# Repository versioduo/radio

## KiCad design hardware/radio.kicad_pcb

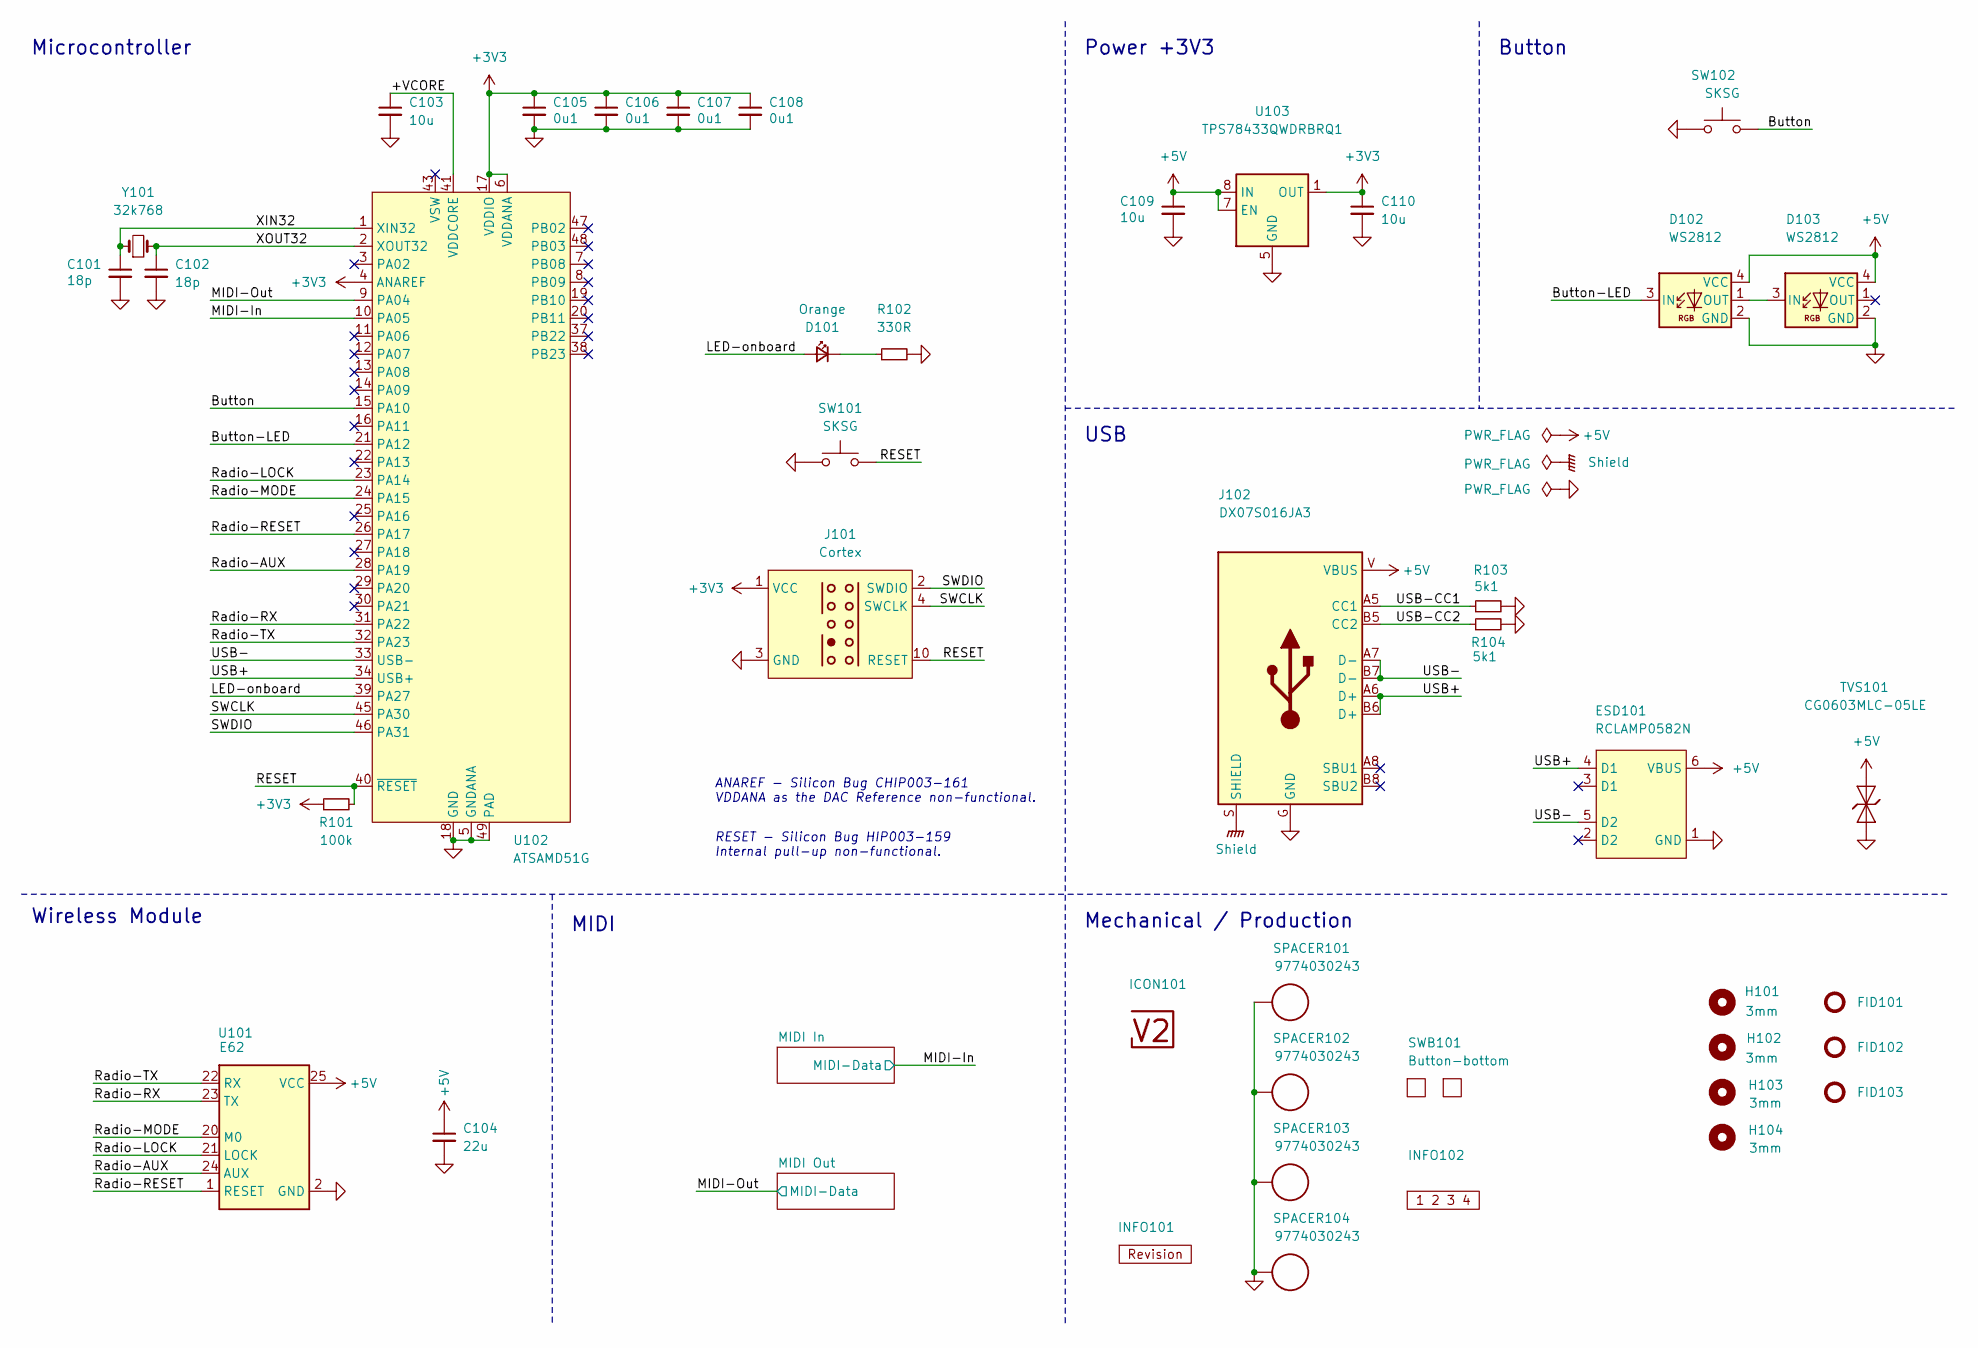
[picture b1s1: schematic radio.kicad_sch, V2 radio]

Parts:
C101, C102: 18p; C_0603; Rating 50V; Mouser 810-CGA3E2C0G1H180J
C103: 10u; C_0603; Rating 10V; Mouser 810-C1608X6S1A106M
C104: 22u; C_1210; Rating 25V; Mouser 810-CGA6P3X7R1E226M5
C105, C106, C107, C108: 0u1; C_0603; Rating 50V; Mouser 810-CGA3E2X7R1H104MA
C109, C110: 10u; C_0805; Rating 25V; Mouser 810-C2012X5R1E106K
D101: Orange; LED_0603; Rating 605nm; Mouser 755-SML-D12D1WT86
D102, D103: WS2812; WS2812-2020; Rating 15mA; LCSC C965555
ESD101: RCLAMP0582N; SLP1210N6; Rating 20kV; Mouser 947-RCLAMP0582N.TCT
FID101, FID102, FID103: Fiducial_Paste; Fiducial_0.5mm_Mask1mm_Paste
H101, H102, H103, H104: 3mm; MountingHole_3mm
ICON101: V2-logo; Logo_Small
INFO101: Revision
INFO102: Layer_Numbers
J101: Cortex
J102: DX07S016JA3; JAE_DX07S016JA3; Rating USB2.0; Mouser 656-DX07S016JA3R1500
R101: 100k; R_0603; Rating 100mW; Mouser 71-CRCW0603100KFKEAC
R102: 330R; R_0603; Rating 100mW; Mouser 71-CRCW0603330RFKEAC
R103, R104: 5k1; R_0603; Rating 100mW; Mouser 71-CRCW06035K10FKEAC
SPACER101, SPACER102, SPACER103, SPACER104: 9774030243; Rating 3mm; Mouser 710-9774030243R
SW101, SW102: SKSG; Rating 1.6N; Mouser 688-SKSGACE010
SWB101: Button-bottom; PCB_Button-bottom
TVS101: CG0603MLC-05LE; D_0603; Rating 5V; Mouser 652-CG0603MLC-05LE
U101: E62; Rating 433Mhz
U102: ATSAMD51G; QFN-48-1EP_7x7mm_P0.5mm_EP5.45x5.45mm_ThermalVias; Rating Cortex-M4F; Mouser 556-ATSAMD51G19AMU
U103: TPS78433QWDRBRQ1; VSON-8-1_3x3mm_P0.65_EP1.65x2.4mm; Rating 300mA; Mouser 595-TPS78433QWDRBRQ1
Y101: 32k768; Crystal_SMD_3215-2Pin_3.2x1.5mm; Rating 10ppm; Mouser 815-ABS0716632.768KT

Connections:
+3V3: C105.1, C106.1, C107.1, C108.1, C110.1, J101.1 (VCC), R101.1, U102.4 (ANAREF), U102.6 (VDDANA), U102.17 (VDDIO), U102.36 (VDDIO), U102.44 (VDDIO), U103.1 (OUT); also elsewhere on the board
+5V: C104.1, C109.1, D102.4 (VCC), D103.4 (VCC), ESD101.6 (VBUS), J102.V (VBUS), TVS101.2 (A), U101.25 (VCC), U103.7 (EN), U103.8 (IN); also elsewhere on the board
/+VCORE: C103.1, U102.41 (VDDCORE)
/Button: SW102.2, U102.15 (PA10)
/Button-LED: D102.3 (IN), U102.21 (PA12)
/LED-onboard: D101.2 (A), U102.39 (PA27)
/MIDI-In: U102.10 (PA05); also elsewhere on the board
/MIDI-Out: U102.9 (PA04); also elsewhere on the board
/RESET: J101.10 (RESET), R101.2, SW101.2, U102.40 (~RESET)
/Radio-AUX: U101.24 (AUX), U102.28 (PA19)
/Radio-LOCK: U101.21 (LOCK), U102.23 (PA14)
/Radio-MODE: U101.20 (M0), U102.24 (PA15)
/Radio-RESET: U101.1 (RESET), U102.26 (PA17)
/Radio-RX: U101.23 (TX), U102.31 (PA22)
/Radio-TX: U101.22 (RX), U102.32 (PA23)
/SWCLK: J101.4 (SWCLK), U102.45 (PA30)
/SWDIO: J101.2 (SWDIO), U102.46 (PA31)
/Shield: J102.S (SHIELD)
/USB+: ESD101.4 (D1), J102.A6 (D+), J102.B6 (D+), U102.34 (USB+)
/USB-: ESD101.5 (D2), J102.A7 (D-), J102.B7 (D-), U102.33 (USB-)
/USB-CC1: J102.A5 (CC1), R103.1
/USB-CC2: J102.B5 (CC2), R104.1
/XIN32: C101.1, U102.1 (XIN32), Y101.1
/XOUT32: C102.1, U102.2 (XOUT32), Y101.2
GND: C101.2, C102.2, C103.2, C104.2, C105.2, C106.2, C107.2, C108.2, C109.2, C110.2, D102.2 (GND), D103.2 (GND), ESD101.1 (GND), J101.3 (GND), J101.5 (GND), J102.G (GND), R102.2, R103.2, R104.2, SPACER101.1 (1_1), SPACER102.1 (1_1), SPACER103.1 (1_1), SPACER104.1 (1_1), SW101.1, SW102.1, TVS101.1 (K), U101.2 (GND), U101.8 (GND), U101.11 (GND), U101.13 (GND), U101.14 (GND), U101.15 (GND), U101.16 (GND), U101.19 (GND), U101.26 (GND), U102.5 (GNDANA), U102.18 (GND), U102.35 (GND), U102.42 (GND), U102.49 (PAD), U103.5 (GND), U103.9 (GND); also elsewhere on the board
unnamed: D101.1 (K), R102.1
unnamed: D102.1 (OUT), D103.3 (IN)

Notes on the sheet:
ANAREF - ﻿Silicon Bug CHIP003-161 VDDANA as the DAC Reference non-functional.
Wireless Module
RESET - ﻿Silicon Bug HIP003-159 Internal pull-up non-functional.
Button
Power +3V3
Mechanical / Production
Microcontroller
USB
MIDI

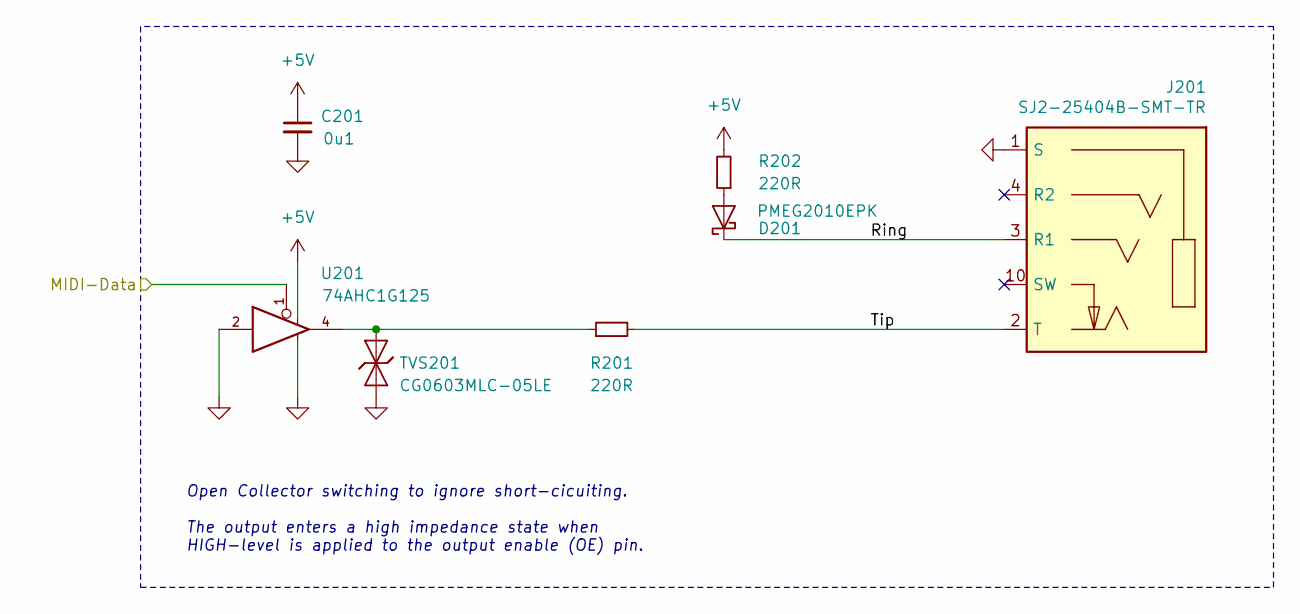
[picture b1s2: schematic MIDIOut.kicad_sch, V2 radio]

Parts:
C201: 0u1; C_0603; Rating 50V; Mouser 810-CGA3E2X7R1H104MA
D201: PMEG2010EPK; D_SOD-1608; Rating 20V; Mouser 771-PMEG2010EPK
J201: SJ2-25404B-SMT-TR; CUI_SJ2-25404B-SMT-TR; Rating 2.5mm; Mouser 490-SJ2-25404BSMT-TR
R201, R202: 220R; R_0603; Rating 330mW; Mouser 71-CRCW0603220RFKEAH
TVS201: CG0603MLC-05LE; D_0603; Rating 5V; Mouser 652-CG0603MLC-05LE
U201: 74AHC1G125; SOT-23-5; Rating 8mA; Mouser 595-SN74AHC1G125DBVR

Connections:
+5V: C201.1, R202.2, U201.5; also elsewhere on the board
/MIDI Out/Ring: D201.1 (K), J201.3 (R1)
/MIDI Out/Tip: J201.2 (T), R201.2
/MIDI-Out: U201.1; also elsewhere on the board
GND: C201.2, J201.1 (S), TVS201.1 (K), U201.2, U201.3; also elsewhere on the board
unnamed: D201.2 (A), R202.1
unnamed: R201.1, TVS201.2 (A), U201.4

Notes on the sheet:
﻿Open Collector switching to ignore short-cicuiting. The output enters a high impedance state when HIGH-level is applied to the output enable (OE) pin.

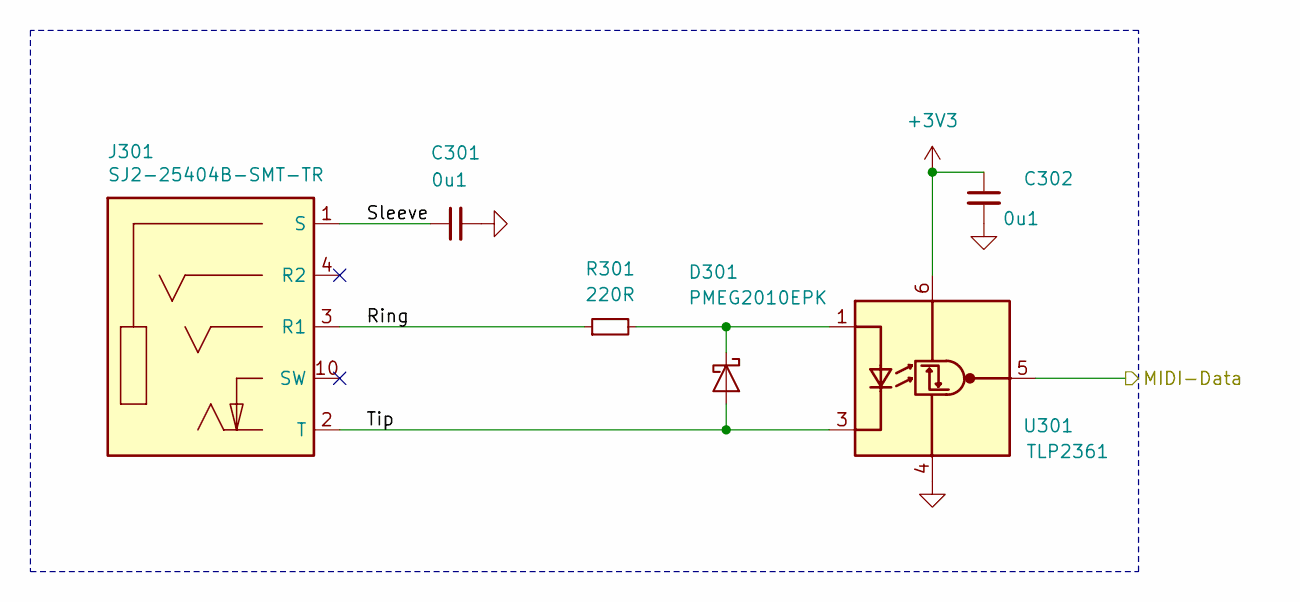
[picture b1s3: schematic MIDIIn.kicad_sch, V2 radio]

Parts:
C301, C302: 0u1; C_0603; Rating 50V; Mouser 810-CGA3E2X7R1H104MA
D301: PMEG2010EPK; D_SOD-1608; Rating 20V; Mouser 771-PMEG2010EPK
J301: SJ2-25404B-SMT-TR; CUI_SJ2-25404B-SMT-TR; Rating 2.5mm; Mouser 490-SJ2-25404BSMT-TR
R301: 220R; R_0603; Rating 330mW; Mouser 71-CRCW0603220RFKEAH
U301: TLP2361; SO-5-6_4.55x3.7mm_P1.27mm; Rating 15Mbps; Mouser 757-TLP2361TPRE

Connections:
+3V3: C302.1, U301.6 (VDD); also elsewhere on the board
/MIDI In/Ring: J301.3 (R1), R301.1
/MIDI In/Sleeve: C301.1, J301.1 (S)
/MIDI In/Tip: D301.2 (A), J301.2 (T), U301.3 (K)
/MIDI-In: U301.5 (VO); also elsewhere on the board
GND: C301.2, C302.2, U301.4 (GND); also elsewhere on the board
unnamed: D301.1 (K), R301.2, U301.1 (A)

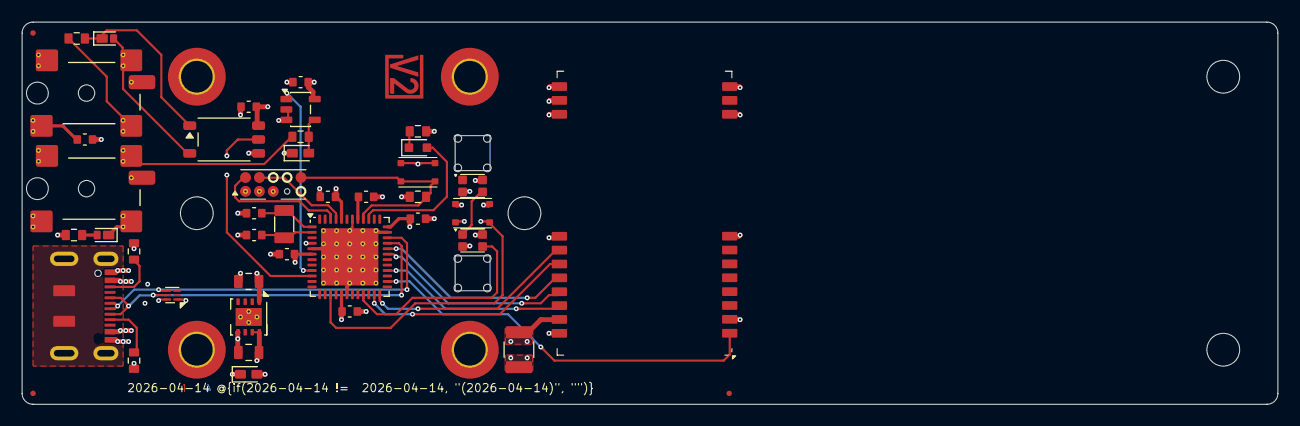
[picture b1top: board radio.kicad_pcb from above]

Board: 4 copper layers, 115.0 x 35.0 mm, 55 parts (0 on the bottom side), 34 nets.

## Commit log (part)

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2025-12-29 Import
2025-12-29 Colour
2026-01-19 Refresh
2026-02-13 Replace Order_Number
2026-02-15 Update Library
2026-03-14 Update ESD suppressor
2026-03-30 Replace diode
2026-05-11 Good Bye Imperial
2026-06-23 Update V2MIDI API
